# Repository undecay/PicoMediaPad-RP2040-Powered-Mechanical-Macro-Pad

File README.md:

RP2040 Wireless Mechanical Macro Pad for Windows and macOS This project turns a 4-key mechanical switch matrix and a standard rotary encoder into a high-performance USB macro pad and media controller. It functions as a native wired USB HID device to control shortcuts and volume across Windows, macOS, and Linux.
//Features
  - Works natively as a USB HID keyboard device, no custom software required.
  -  Anti-ghosting key matrix uses individual switching diodes to prevent current bleed and ensure full n-key rollover.
  -  Dedicated quadrature encoder integration provides smooth, real-time volume adjustment.Compact PCB design optimized for standard Cherry MX footprints and clean signal routing.
//Hardware Required
  - Raspberry Pi Pico (RP2040)
  - 4x Cherry MX (or compatible) mechanical switches
  - 4x 1N4148 switching diodes
  - EC11 Rotary Encoder with push switch
  - Custom PCB Board
  - Micro-USB cable for power and data
//Software Setup
  - [Active Development] Firmware and project sketch files are currently being written. The software stack will utilize the standard Arduino IDE framework with USB HID keyboard and encoder libraries to map the matrix layout.
//Usage
  - Once firmware development is complete, plugging the PicoMediaPad into your computer via USB will automatically enumerate it as a keyboard, allowing you to use your macro keys and control volume instantly.

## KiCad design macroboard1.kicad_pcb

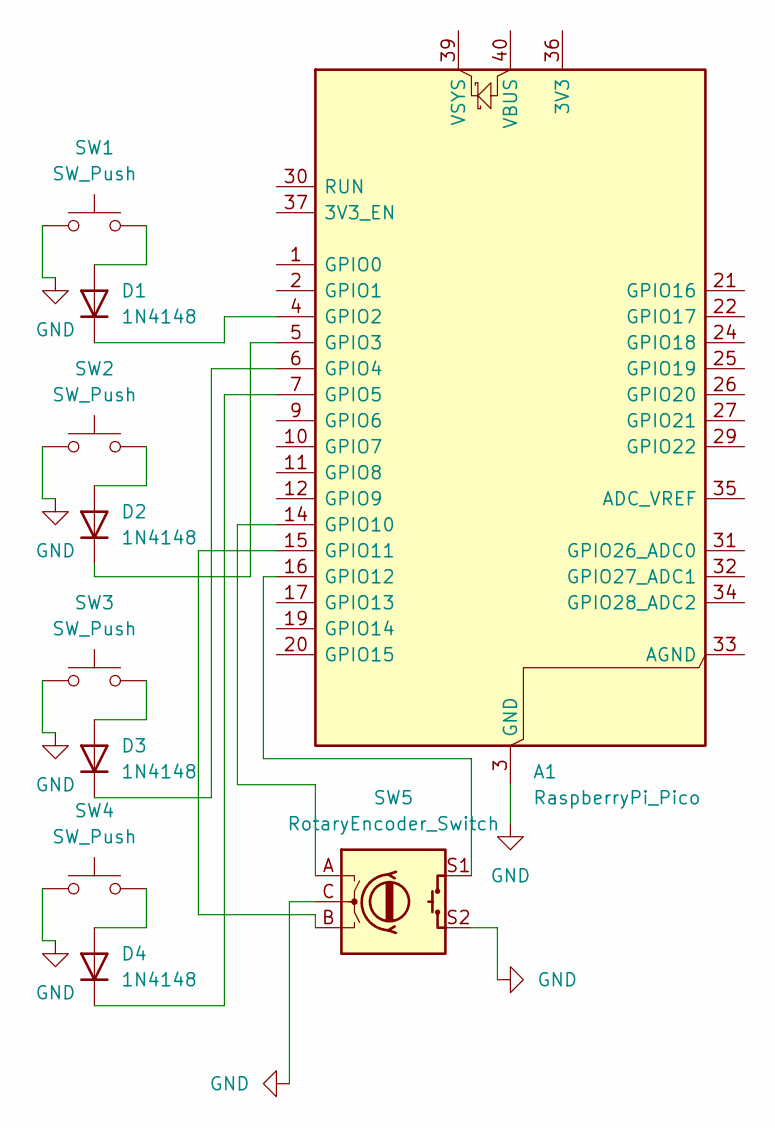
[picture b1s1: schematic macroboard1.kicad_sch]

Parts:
A1: RaspberryPi_Pico; RaspberryPi_Pico_Common_THT
D1, D2, D3, D4: 1N4148; D_DO-35_SOD27_P7.62mm_Horizontal
SW1, SW2, SW3, SW4: SW_Push; MXOnly-1U-Hotswap
SW5: RotaryEncoder_Switch; RotaryEncoder_Alps_EC11E-Switch_Vertical_H20mm

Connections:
GND: A1.3 (GND), A1.8 (GND), A1.13 (GND), A1.18 (GND), A1.23 (GND), A1.28 (GND), A1.38 (GND), SW1.1, SW2.1, SW3.1, SW4.1, SW5.C, SW5.S2
unnamed: A1.4 (GPIO2), D1.1 (K)
unnamed: A1.5 (GPIO3), D2.1 (K)
unnamed: A1.6 (GPIO4), D3.1 (K)
unnamed: A1.7 (GPIO5), D4.1 (K)
unnamed: A1.14 (GPIO10), SW5.A
unnamed: A1.15 (GPIO11), SW5.B
unnamed: A1.16 (GPIO12), SW5.S1
unnamed: D1.2 (A), SW1.2
unnamed: D2.2 (A), SW2.2
unnamed: D3.2 (A), SW3.2
unnamed: D4.2 (A), SW4.2

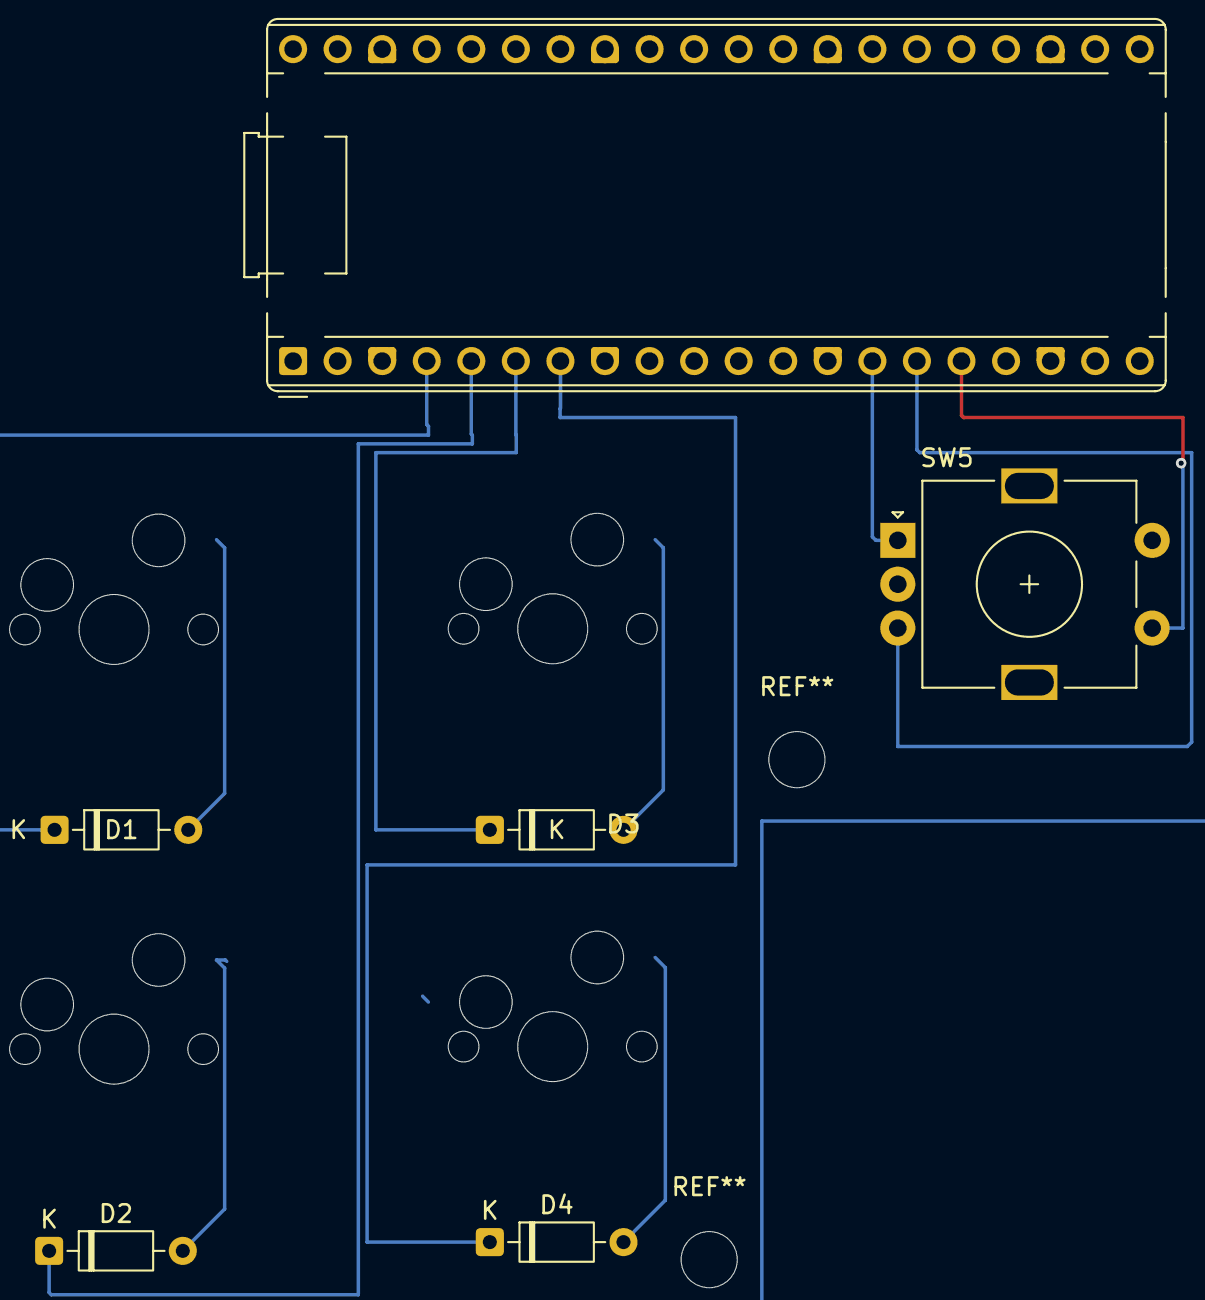
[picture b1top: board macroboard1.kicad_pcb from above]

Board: 2 copper layers, 10 parts (0 on the bottom side), 12 nets.

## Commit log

2026-05-24 Add files via upload
    screenshots of schematics and pcb 3d viewer
2026-05-24 Rename Screenshot 2026-05-24 003611.png to schematic view
2026-05-24 Rename Screenshot 2026-05-24 003728.png to pcb 3d viewer view
2026-05-24 Rename Screenshot 2026-05-24 003802.png to pcb editor view
